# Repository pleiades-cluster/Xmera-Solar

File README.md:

# Xmera-Solar
The Official Solar Design on PROVES Xmera

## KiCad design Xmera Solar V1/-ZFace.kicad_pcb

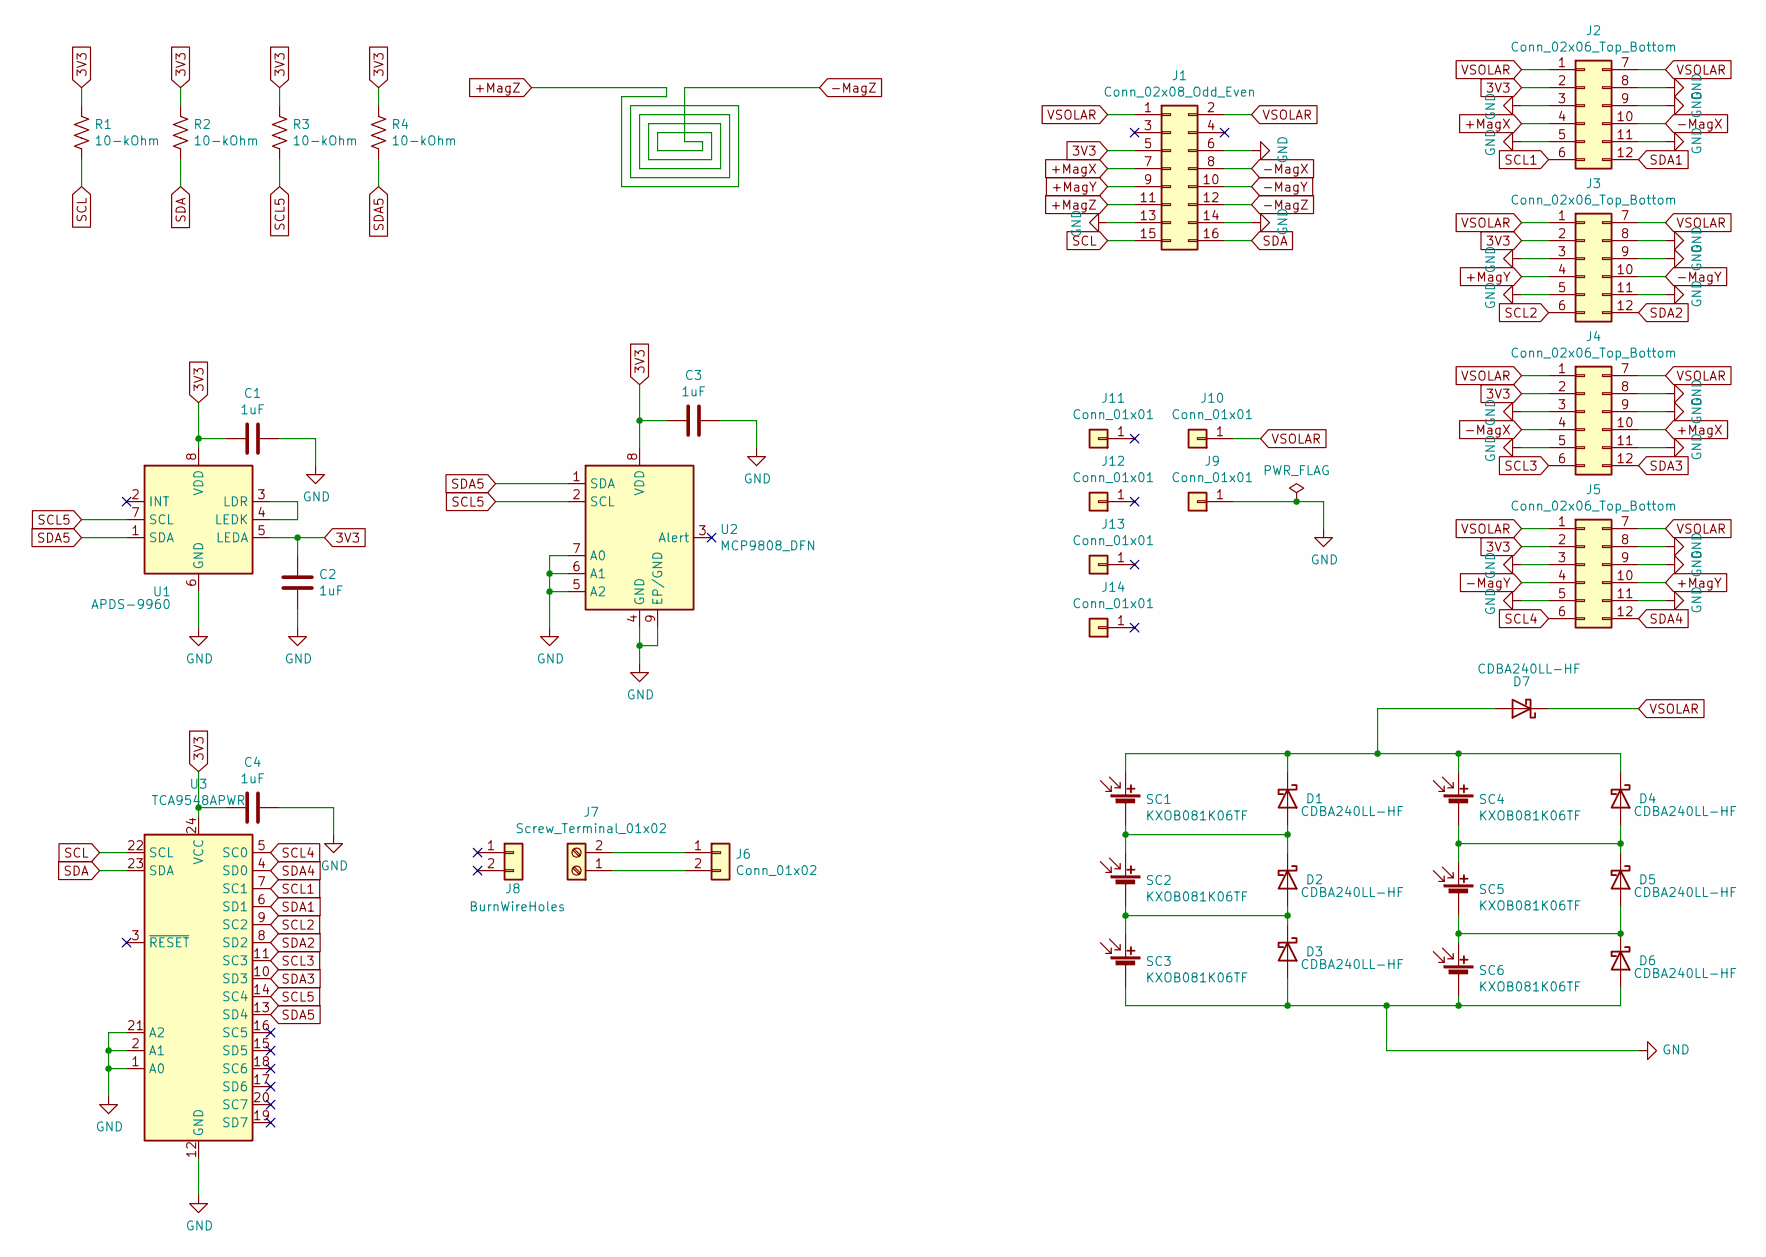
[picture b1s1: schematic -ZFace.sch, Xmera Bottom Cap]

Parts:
C1, C2, C3, C4: 1uF; C_0805_2012Metric
D1, D2, D3, D4, D5, D6, D7: CDBA240LL-HF; DO-214AC
J1: Conn_02x08_Odd_Even; 2x08_P1.27mm_Vertical_SMD
J2, J3, J4, J5: Conn_02x06_Top_Bottom; M55-7101242R(BottomCap)
J6: Conn_01x02; JSTB2B-ZRLFSN
J7: Screw_Terminal_01x02; ScrewTerminal
J8: BurnWireHoles
J9, J10: Conn_01x01; TestPoint_Pad_2.0x2.0mm
J11, J12, J13, J14: Conn_01x01; MountingHoles
R1, R2, R3, R4: 10-kOhm; R_0603_1608Metric
SC1, SC2, SC3, SC4, SC5, SC6: KXOB081K06TF; KXOB201K04F-TR
U1: APDS-9960
U2: MCP9808_DFN; MCP9808-NoLeadPackage
U3: TCA9548APWR; TSSOP-24_4.4x7.8mm_P0.65mm

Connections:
3V3: C1.1, C2.2, C3.1, C4.1, J1.5, J2.2, J3.2, J4.2, J5.2, R1.1, R2.1, R3.1, R4.1, U1.5 (LEDA), U1.8 (VDD), U2.8 (VDD), U3.24 (VCC)
+MagX: J1.7, J2.4, J4.10
+MagY: J1.9, J3.4, J5.10
+MagZ: J1.11, J1.12
-MagX: J1.8, J2.10, J4.4
-MagY: J1.10, J3.10, J5.4
GND: C1.2, C2.1, C3.2, C4.2, D3.2 (A), D6.2 (A), J1.6, J1.13, J1.14, J2.3, J2.5, J2.8, J2.9, J2.11, J3.3, J3.5, J3.8, J3.9, J3.11, J4.3, J4.5, J4.8, J4.9, J4.11, J5.3, J5.5, J5.8, J5.9, J5.11, J9.1, SC3.2 (-), SC6.2 (-), U1.6 (GND), U2.4 (GND), U2.5 (A2), U2.6 (A1), U2.7 (A0), U2.9 (EP/GND), U3.1 (A0), U3.2 (A1), U3.12 (GND), U3.21 (A2)
unnamed: D1.1 (K), D4.1 (K), D7.2 (A), SC1.1 (+), SC4.1 (+)
unnamed: D1.2 (A), D2.1 (K), SC1.2 (-), SC2.1 (+)
unnamed: D2.2 (A), D3.1 (K), SC2.2 (-), SC3.1 (+)
unnamed: D4.2 (A), D5.1 (K), SC4.2 (-), SC5.1 (+)
unnamed: D5.2 (A), D6.1 (K), SC5.2 (-), SC6.1 (+)
unnamed: J6.1, J7.2
unnamed: J6.2, J7.1
unnamed: U1.3 (LDR), U1.4 (LEDK)
SCL: J1.15, R1.2, U3.22 (SCL)
SCL1: J2.6, U3.7 (SC1)
SCL2: J3.6, U3.9 (SC2)
SCL3: J4.6, U3.11 (SC3)
SCL4: J5.6, U3.5 (SC0)
SCL5: R3.2, U1.7 (SCL), U2.2 (SCL), U3.14 (SC4)
SDA: J1.16, R2.2, U3.23 (SDA)
SDA1: J2.12, U3.6 (SD1)
SDA2: J3.12, U3.8 (SD2)
SDA3: J4.12, U3.10 (SD3)
SDA4: J5.12, U3.4 (SD0)
SDA5: R4.2, U1.1 (SDA), U2.1 (SDA), U3.13 (SD4)
VSOLAR: D7.1 (K), J1.1, J1.2, J2.1, J2.7, J3.1, J3.7, J4.1, J4.7, J5.1, J5.7, J10.1

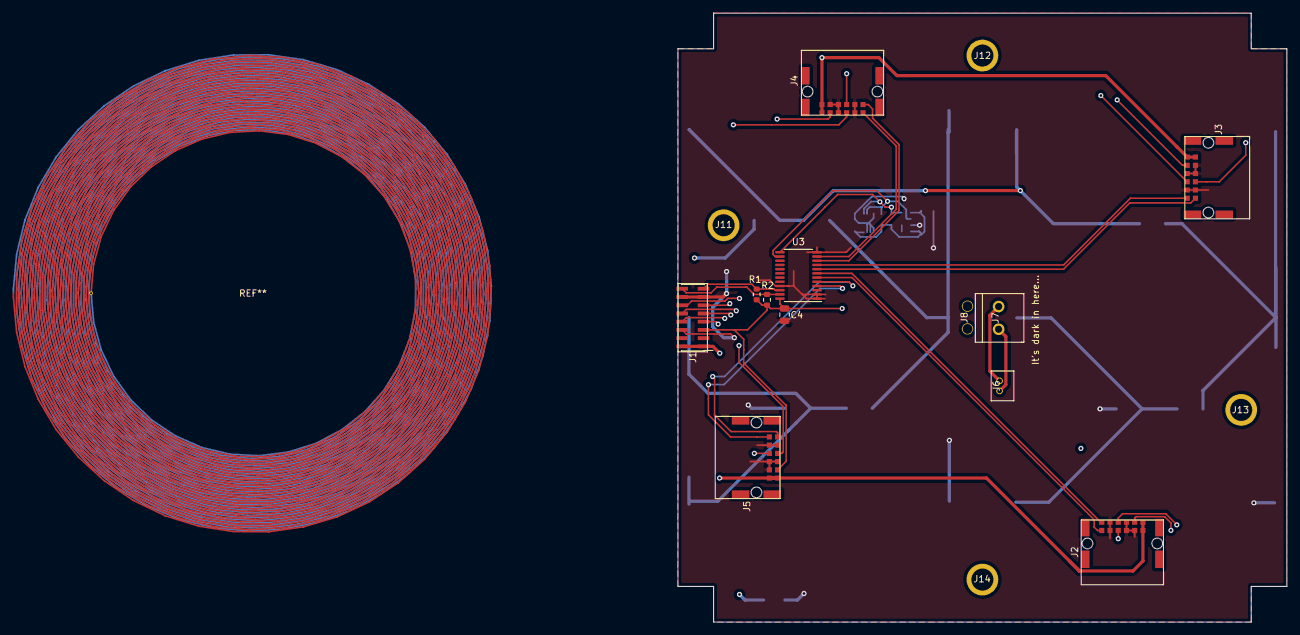
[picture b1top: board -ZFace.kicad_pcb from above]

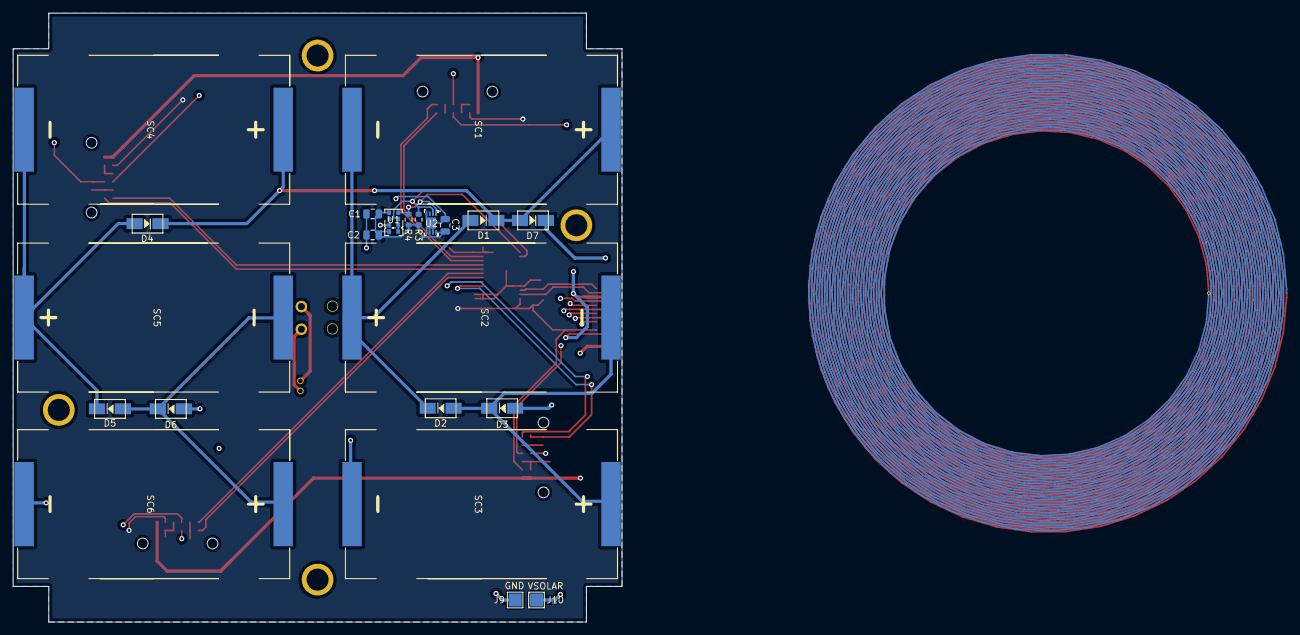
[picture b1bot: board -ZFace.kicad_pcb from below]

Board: 4 copper layers, 94.0 x 94.0 mm, 38 parts (22 on the bottom side), 28 nets.

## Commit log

2023-01-31 Xmera V1 Solar Boards
    First iteration of Xmera XY and -Z faces
